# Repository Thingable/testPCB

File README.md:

# testPCB
A quick test for pcb prototyping equipment.

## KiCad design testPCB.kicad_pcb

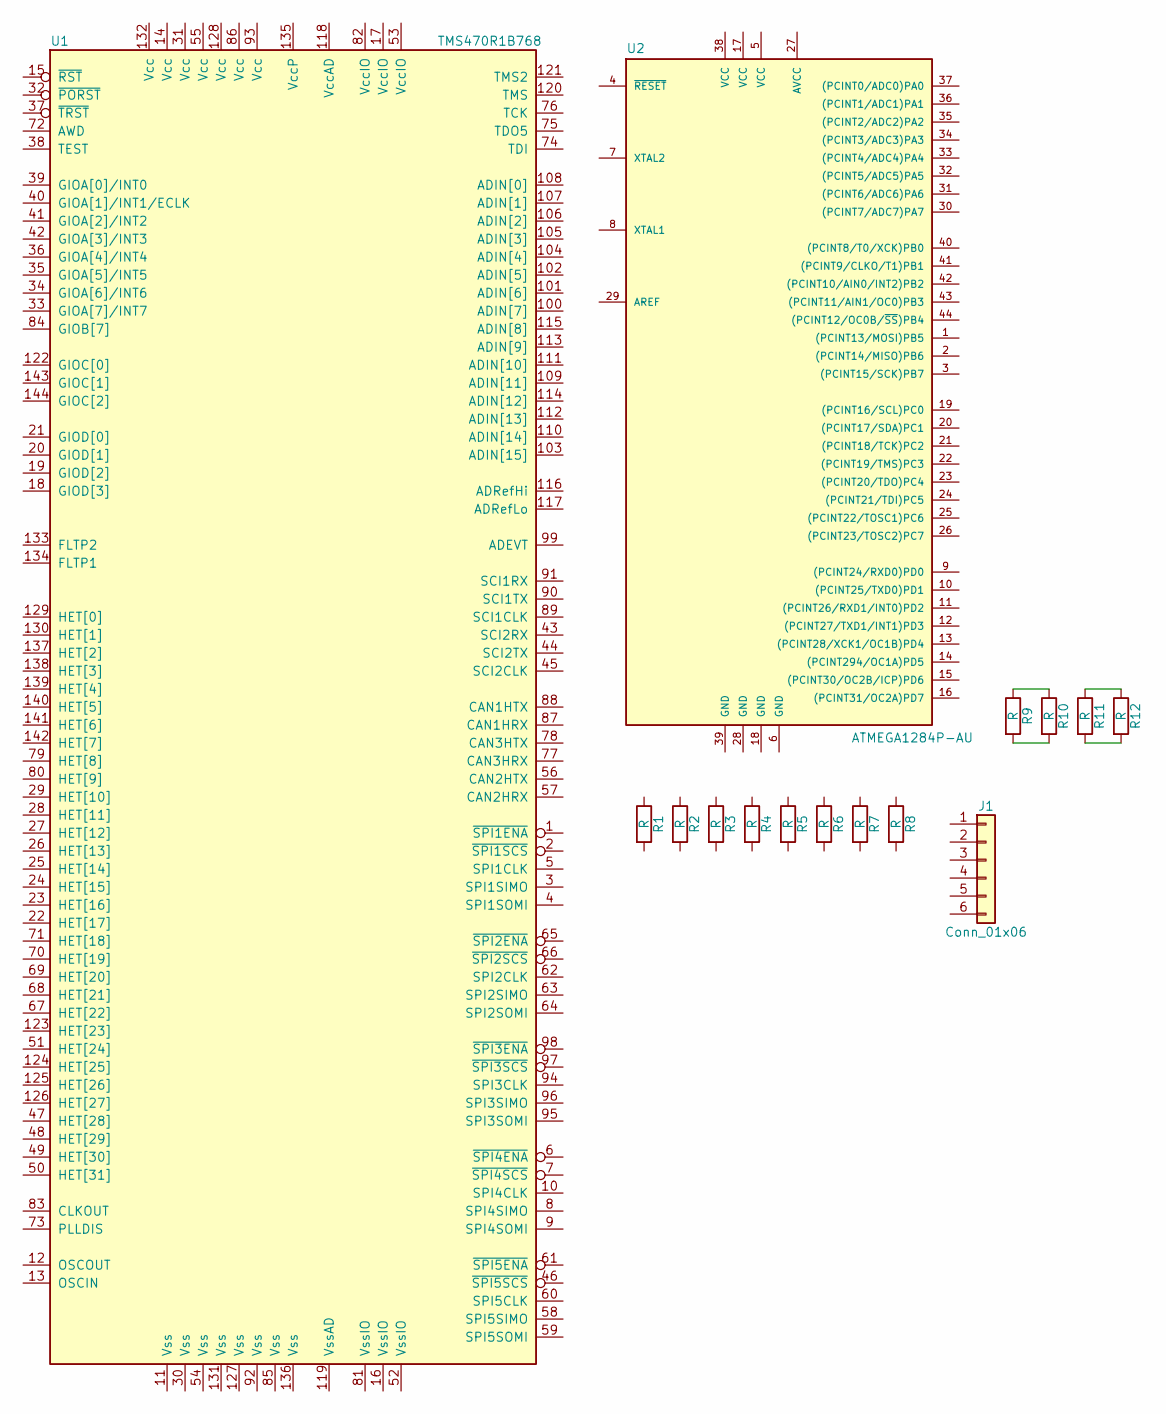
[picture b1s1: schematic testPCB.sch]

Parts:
J1: Conn_01x06; Pin_Header_Straight_1x06_Pitch2.54mm
R1: R; R_0201_NoSilk
R2: R; R_0402_NoSilk
R3: R; R_0603
R4, R9, R10, R11, R12: R; R_0805
R5: R; R_1206
R6: R; R_1812
R7: R; R_2010
R8: R; R_2512
U1: TMS470R1B768; BGA-144-1mm
U2: ATMEGA1284P-AU; TQFP-44_10x10mm_Pitch0.8mm

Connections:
unnamed: R9.1, R10.1
unnamed: R9.2, R10.2
unnamed: R11.1, R12.1
unnamed: R11.2, R12.2

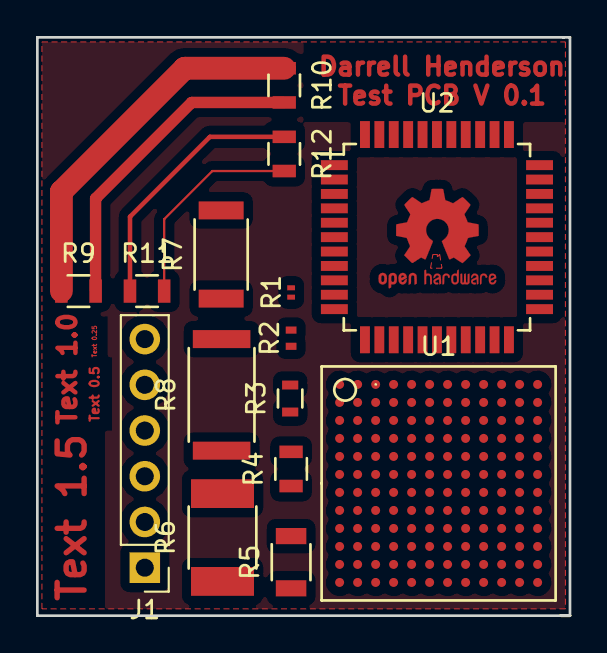
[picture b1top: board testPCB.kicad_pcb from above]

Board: 2 copper layers, 29.6 x 32.1 mm, 15 parts (0 on the bottom side), 4 nets.

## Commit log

2018-03-24 Initial committ
2018-03-24 Add some images.
